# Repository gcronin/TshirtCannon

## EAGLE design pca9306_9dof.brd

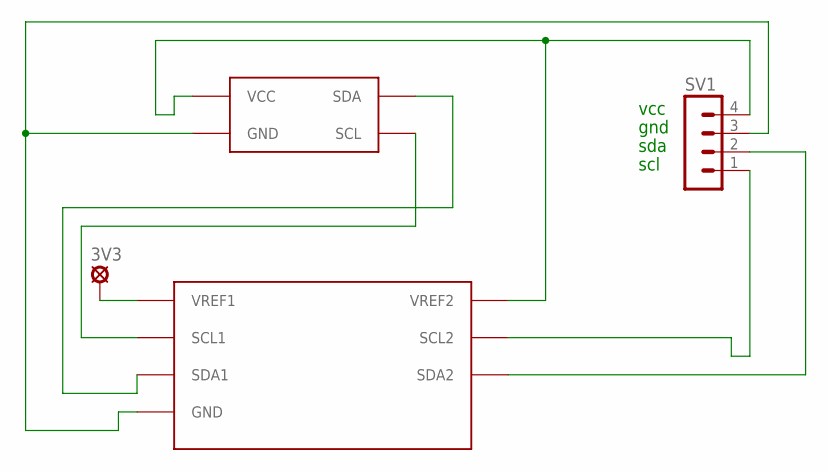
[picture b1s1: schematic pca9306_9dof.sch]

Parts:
3V3: LSP11
SV1: MA04-1
U$1: PCA9306
U$2: 9DOF

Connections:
unnamed: SV1.3, U$1.GND, U$2.GND
unnamed: SV1.4, U$1.VREF2, U$2.VCC
unnamed: SV1.2, U$1.SDA2
unnamed: SV1.1, U$1.SCL2
unnamed: U$1.SDA1, U$2.SDA
unnamed: U$1.SCL1, U$2.SCL
unnamed: 3V3.MP, U$1.VREF1

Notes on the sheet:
vcc
gnd
sda
scl

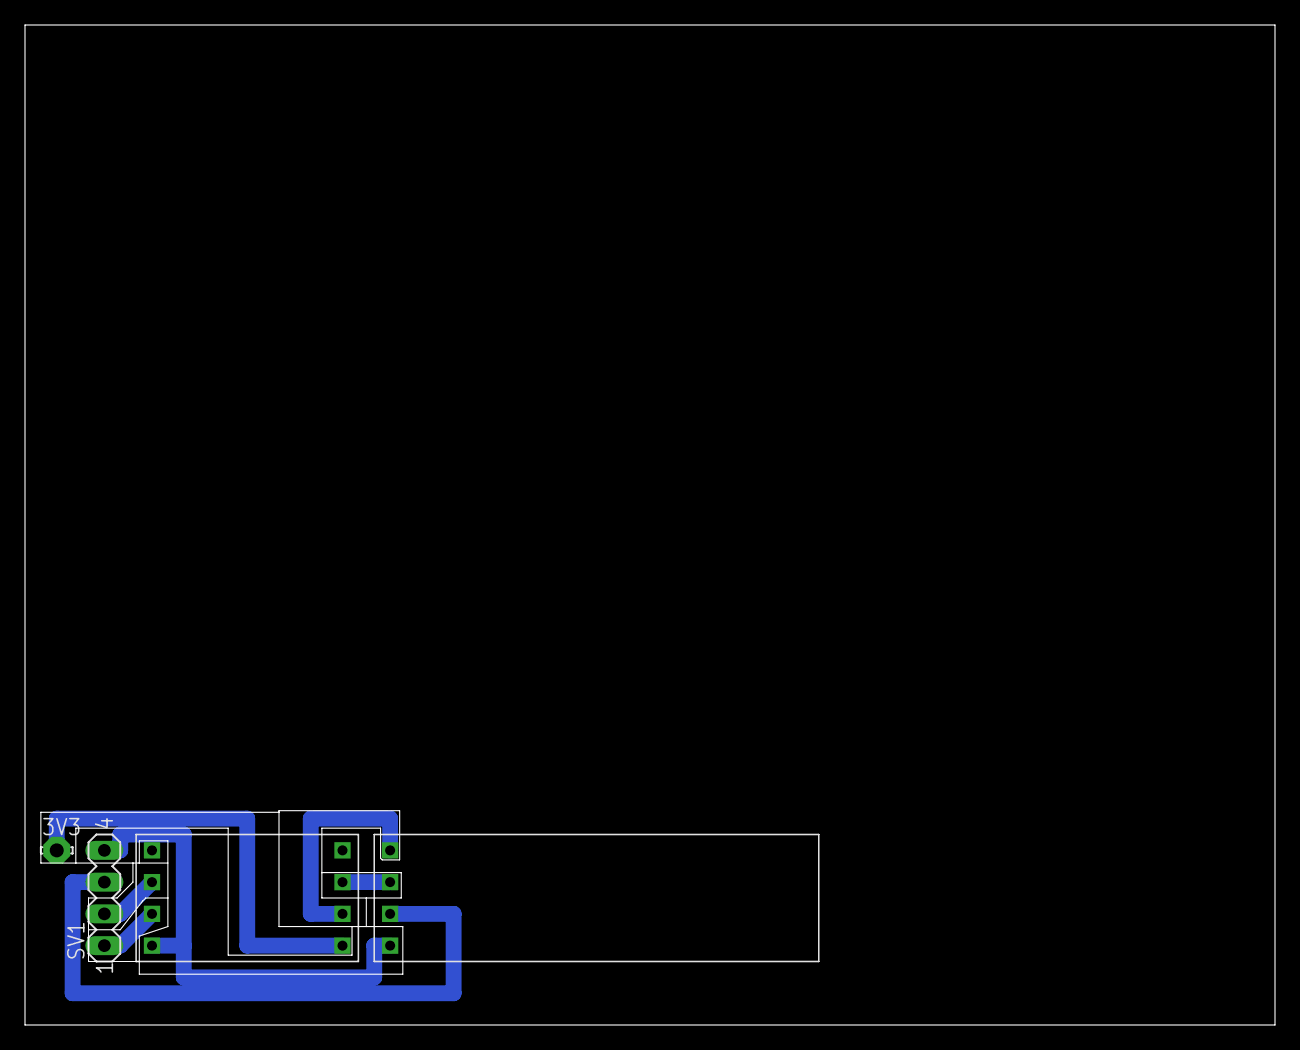
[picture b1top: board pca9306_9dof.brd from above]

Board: 2 copper layers, 100.0 x 80.0 mm, 4 parts (0 on the bottom side), 7 nets.

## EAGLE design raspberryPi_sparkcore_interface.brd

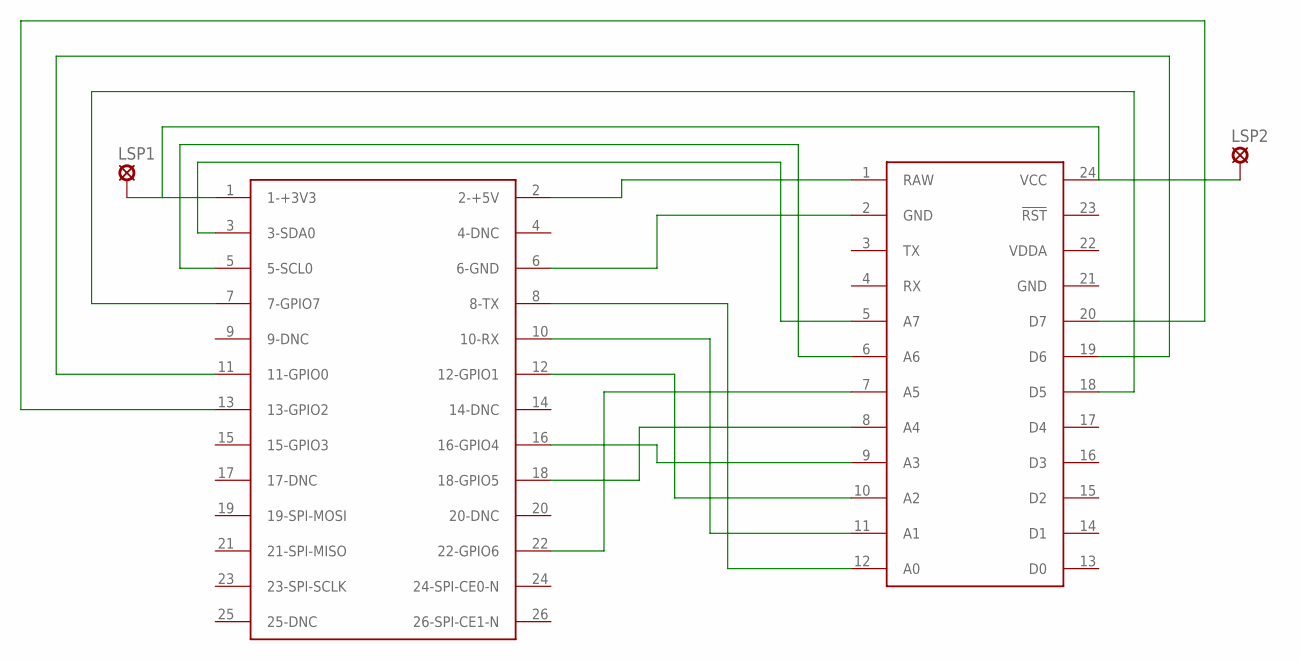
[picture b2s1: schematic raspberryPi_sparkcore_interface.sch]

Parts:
LSP1, LSP2: MCS08
U$1: RASPBERRY-PI
U$2: SPARK_CORECORE; SPARK_CORE

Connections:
GND: U$1.6 (6-GND), U$2.2 (GND), U$2.21 (GND)
unnamed: U$1.2 (2-+5V), U$2.1 (RAW)
unnamed: LSP1.MP, LSP2.MP, U$1.1 (1-+3V3), U$2.24 (VCC)
unnamed: U$1.7 (7-GPIO7), U$2.18 (D5)
unnamed: U$1.11 (11-GPIO0), U$2.19 (D6)
unnamed: U$1.13 (13-GPIO2), U$2.20 (D7)
unnamed: U$1.3 (3-SDA0), U$2.5 (A7)
unnamed: U$1.5 (5-SCL0), U$2.6 (A6)
unnamed: U$1.8 (8-TX), U$2.12 (A0)
unnamed: U$1.10 (10-RX), U$2.11 (A1)
unnamed: U$1.12 (12-GPIO1), U$2.10 (A2)
unnamed: U$1.16 (16-GPIO4), U$2.9 (A3)
unnamed: U$1.18 (18-GPIO5), U$2.8 (A4)
unnamed: U$1.22 (22-GPIO6), U$2.7 (A5)
VDDA: U$2.22 (VDDA)

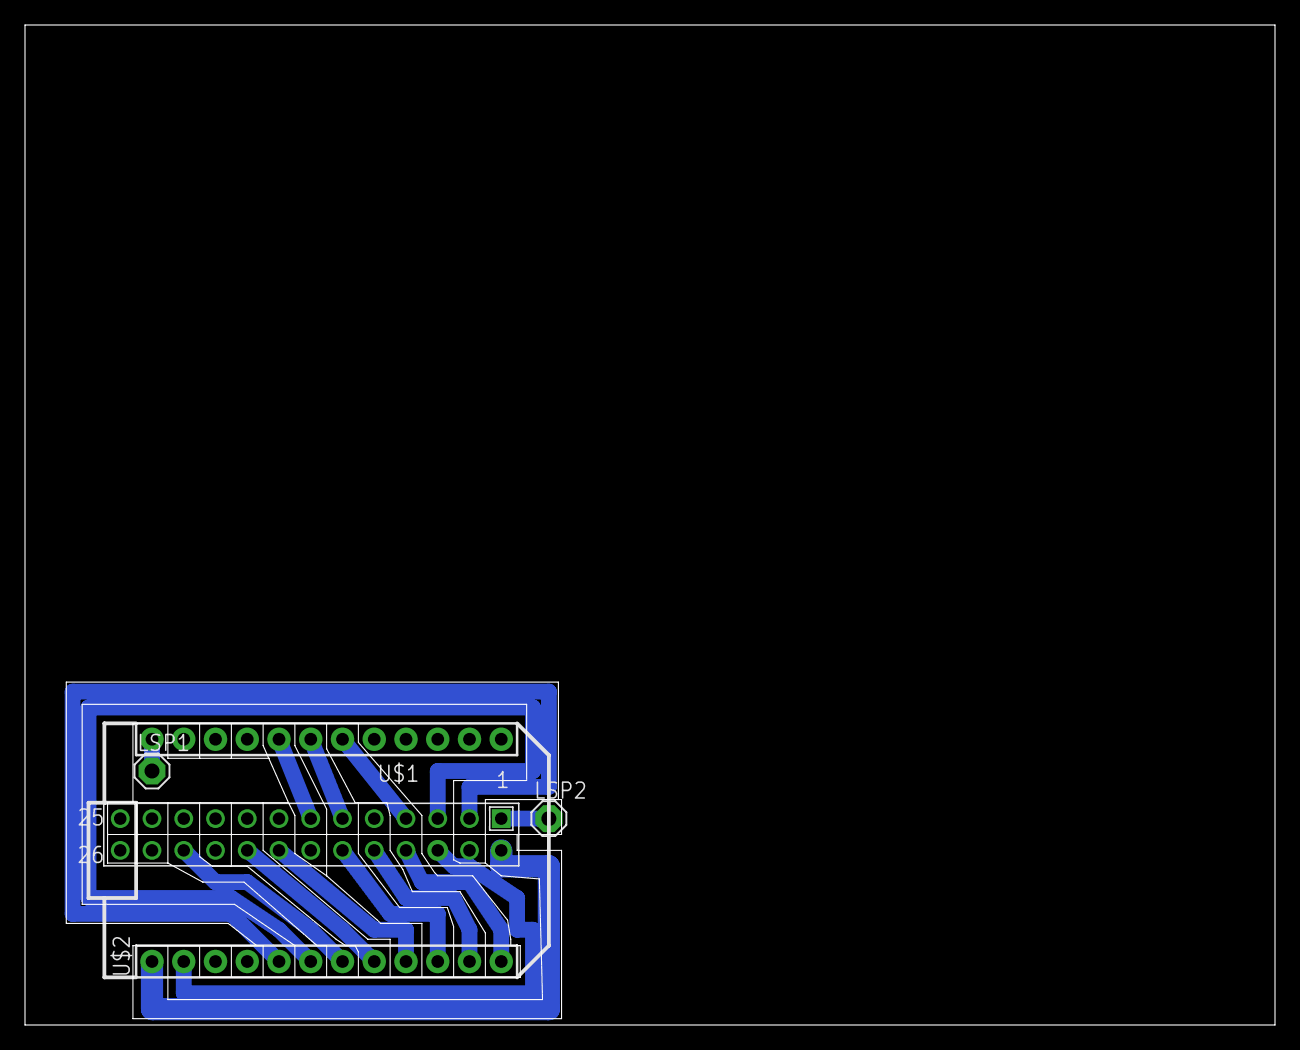
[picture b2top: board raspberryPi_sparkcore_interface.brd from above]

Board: 2 copper layers, 100.0 x 80.0 mm, 4 parts (0 on the bottom side), 14 nets.

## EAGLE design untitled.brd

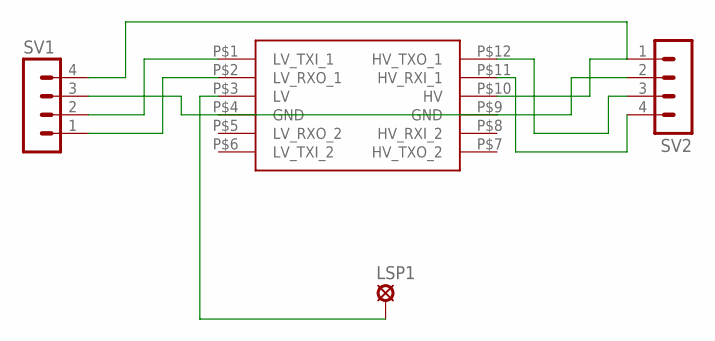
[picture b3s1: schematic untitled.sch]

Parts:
LSP1: MCS08
SV1, SV2: MA04-1
U$1: LOGIC_LEVEL_CONVERTER

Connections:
GND: SV1.3, SV2.2, U$1.P$4 (GND), U$1.P$9 (GND)
unnamed: SV1.1, U$1.P$2 (LV_RXO_1)
unnamed: SV1.2, U$1.P$1 (LV_TXI_1)
unnamed: LSP1.MP, U$1.P$3 (LV)
unnamed: SV1.4, SV2.1, U$1.P$10 (HV)
unnamed: SV2.3, U$1.P$12 (HV_TXO_1)
unnamed: SV2.4, U$1.P$11 (HV_RXI_1)

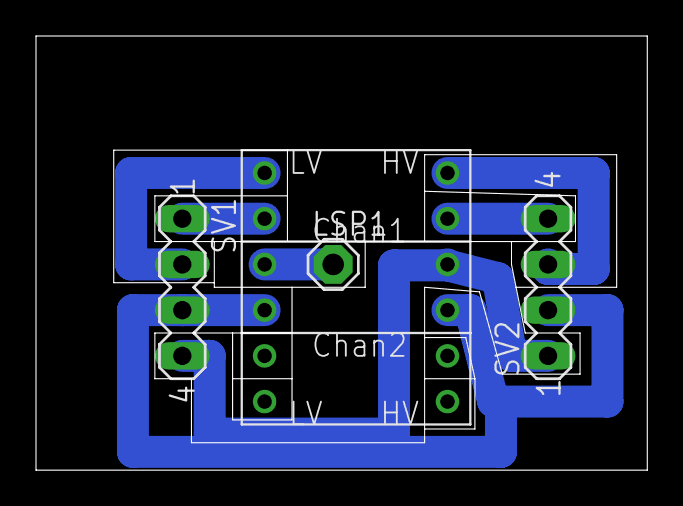
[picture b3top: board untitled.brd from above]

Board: 2 copper layers, 33.9 x 24.1 mm, 4 parts (0 on the bottom side), 7 nets.

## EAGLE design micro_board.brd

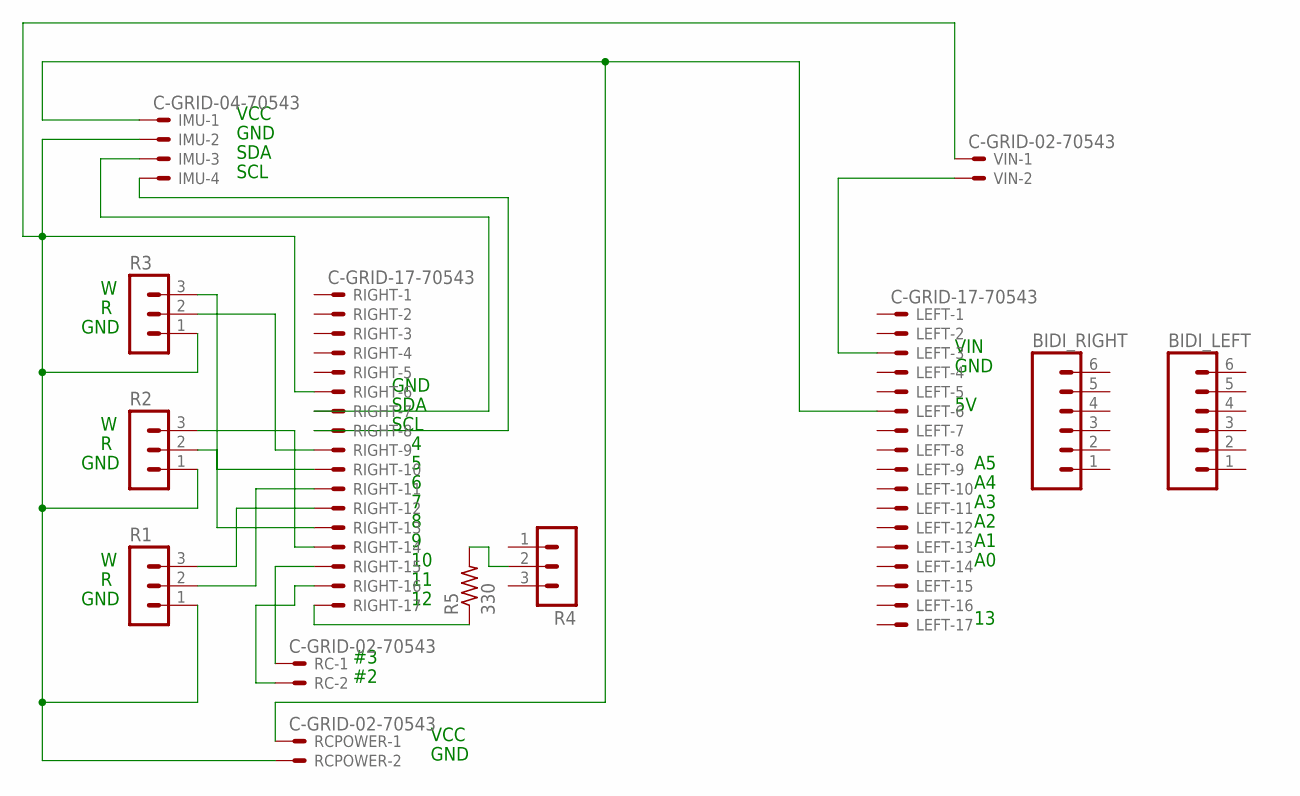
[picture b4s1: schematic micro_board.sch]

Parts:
BIDI_LEFT: M06LONGPADS; 1X06_LONGPADS
BIDI_RIGHT: M06LONGPADS; 1X06_LONGPADS
IMU: C-GRID-04-70543; 70543-04
LEFT: C-GRID-17-70543; 70543-17
R1, R2, R3, R4: MA03-1
R5: 330; 0207/12
RC: C-GRID-02-70543; 70543-02
RCPOWER: C-GRID-02-70543; 70543-02
RIGHT: C-GRID-17-70543; 70543-17
VIN: C-GRID-02-70543; 70543-02

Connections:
5V: IMU.1, LEFT.6, RCPOWER.1
GND: IMU.2, R1.1, R2.1, R3.1, RCPOWER.2, RIGHT.6, VIN.1
unnamed: R3.2, RIGHT.9
unnamed: R2.2, RIGHT.10
unnamed: R1.2, RIGHT.11
unnamed: R1.3, RIGHT.12
unnamed: R3.3, RIGHT.13
unnamed: R2.3, RIGHT.14
unnamed: IMU.3, RIGHT.7
unnamed: IMU.4, RIGHT.8
unnamed: RC.1, RIGHT.15
unnamed: RC.2, RIGHT.16
unnamed: R5.1, RIGHT.17
unnamed: R4.2, R5.2
unnamed: LEFT.3, VIN.2

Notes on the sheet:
GND
SDA
SCL
VIN
VCC

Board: 2 copper layers, 13 parts (0 on the bottom side), 15 nets, no tracks yet.

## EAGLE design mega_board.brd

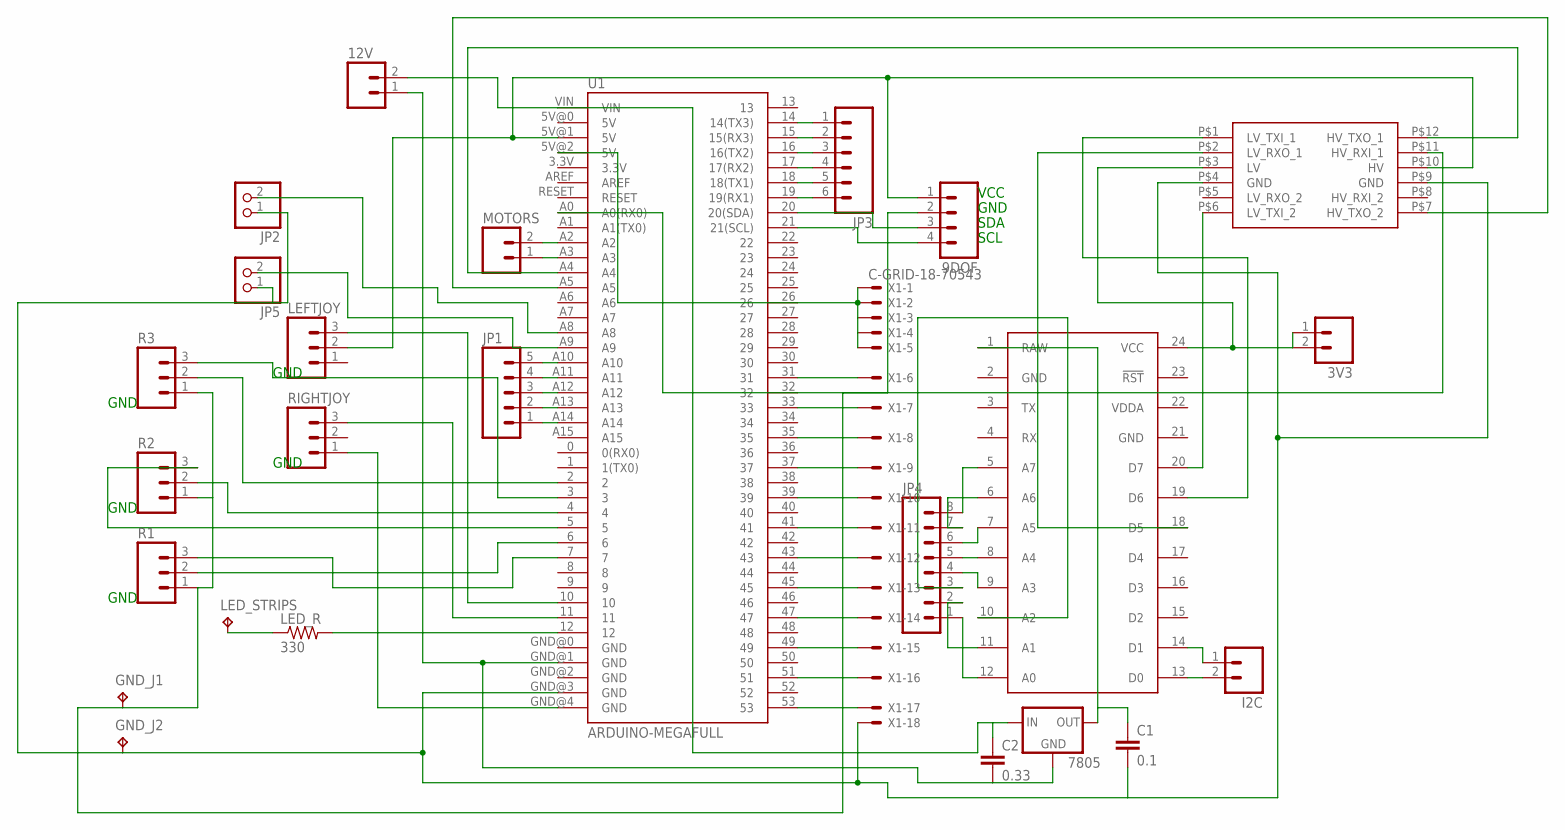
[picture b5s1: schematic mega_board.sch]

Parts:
3V3, 12V: M02PTH3; 1X02_LONGPADS
9DOF: M04LONGPADS; 1X04_LONGPADS
7805: V_REG_78XXSIDE; 78XXL
C1: 0.1; C050-024X044
C2: 0.33; C050-024X044
GND_J1, GND_J2: TPPAD1-17; P1-17
I2C: M02PTH3; 1X02_LONGPADS
JP1: M05PTH_LONGPADS; 1X05_LONGPADS
JP2, JP5: PINHD-1X2; 1X02
JP3: M06LONGPADS; 1X06_LONGPADS
JP4: M08LONGPADS; 1X08_LONGPADS
LED_R: 330; 0207/10
LED_STRIPS: TPPAD1-17; P1-17
LEFTJOY: M03LONGPADS; 1X03_LONGPADS
MOTORS: M02PTH3; 1X02_LONGPADS
R1, R2, R3: M03LONGPADS; 1X03_LONGPADS
RIGHTJOY: M03LONGPADS; 1X03_LONGPADS
U1: ARDUINO-MEGAFULL; ARDUINO_MEGA
U$1: SPARK_CORECORE; SPARK_CORE
U$2: LOGIC_LEVEL_CONVERTER
X1: C-GRID-18-70543; 70543-18

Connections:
5V: 9DOF.1, LEFTJOY.2, U1.5V@1 (5V), U$2.P$10 (HV)
GND: C1.2, GND_J2.TP, JP2.1, JP5.1, U1.GND@3 (GND), U$1.2 (GND), U$1.21 (GND), U$2.P$4 (GND), U$2.P$9 (GND), X1.18
unnamed: 9DOF.4, U1.21 (21(SCL))
unnamed: 9DOF.3, U1.20 (20(SDA))
unnamed: 3V3.1, 3V3.2, U$1.24 (VCC), U$2.P$3 (LV)
unnamed: RIGHTJOY.3, U1.11
unnamed: U1.A4, U$2.P$12 (HV_TXO_1)
unnamed: U1.A5, U$2.P$7 (HV_TXO_2)
unnamed: U$1.20 (D7), U$2.P$6 (LV_TXI_2)
unnamed: U$1.19 (D6), U$2.P$1 (LV_TXI_1)
unnamed: LEFTJOY.3, U1.10
unnamed: JP3.1, U1.14 (14(TX3))
unnamed: JP3.2, U1.15 (15(RX3))
unnamed: JP3.3, U1.16 (16(TX2))
unnamed: JP3.4, U1.17 (17(RX2))
unnamed: JP3.5, U1.18 (18(TX1))
unnamed: JP3.6, U1.19 (19(RX1))
unnamed: JP2.2, U1.A8
unnamed: JP5.2, U1.A9
unnamed: JP1.5, U1.A10
unnamed: JP1.4, U1.A11
unnamed: JP1.3, U1.A12
unnamed: JP1.2, U1.A13
unnamed: JP1.1, U1.A14
unnamed: 12V.2, 7805.IN, C2.1, U1.VIN
unnamed: 12V.1, 7805.GND, C2.2, U1.GND@1 (GND)
unnamed: JP4.8, U$1.5 (A7)
unnamed: JP4.7, U$1.6 (A6)
unnamed: JP4.6, U$1.7 (A5)
unnamed: JP4.5, U$1.8 (A4)
unnamed: JP4.4, U$1.9 (A3)
unnamed: JP4.1, U$1.12 (A0)
unnamed: JP4.2, U$1.11 (A1)
unnamed: JP4.3, U$1.10 (A2)
unnamed: I2C.2, U$1.13 (D0)
unnamed: I2C.1, U$1.14 (D1)
unnamed: 7805.OUT, C1.1, U$1.1 (RAW)
unnamed: RIGHTJOY.1, U1.GND@4 (GND)
unnamed: MOTORS.2, U1.A2
unnamed: MOTORS.1, U1.A3
unnamed: LED_R.2, U1.12
unnamed: LED_R.1, LED_STRIPS.TP
unnamed: R3.3, U1.3
unnamed: 9DOF.2, GND_J1.TP, R1.1, R2.1, R3.1
unnamed: R3.2, U1.2
unnamed: R2.2, U1.4
unnamed: R2.3, U1.5
unnamed: R1.2, U1.6
unnamed: R1.3, U1.7
unnamed: U$1.18 (D5), U$2.P$2 (LV_RXO_1)
unnamed: U1.A0 (A0(RX0)), U$2.P$11 (HV_RXI_1)
unnamed: U1.51, X1.16
unnamed: U1.53, X1.17
unnamed: U1.31, X1.6
unnamed: U1.47, X1.14
unnamed: U1.33, X1.7
unnamed: U1.35, X1.8
unnamed: U1.37, X1.9
unnamed: U1.39, X1.10
unnamed: U1.41, X1.11
unnamed: U1.43, X1.12
unnamed: U1.45, X1.13
unnamed: U1.49, X1.15
unnamed: U1.5V@2 (5V), X1.1, X1.2, X1.3, X1.4, X1.5
VDDA: U$1.22 (VDDA)

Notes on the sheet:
VCC
GND
SDA
SCL

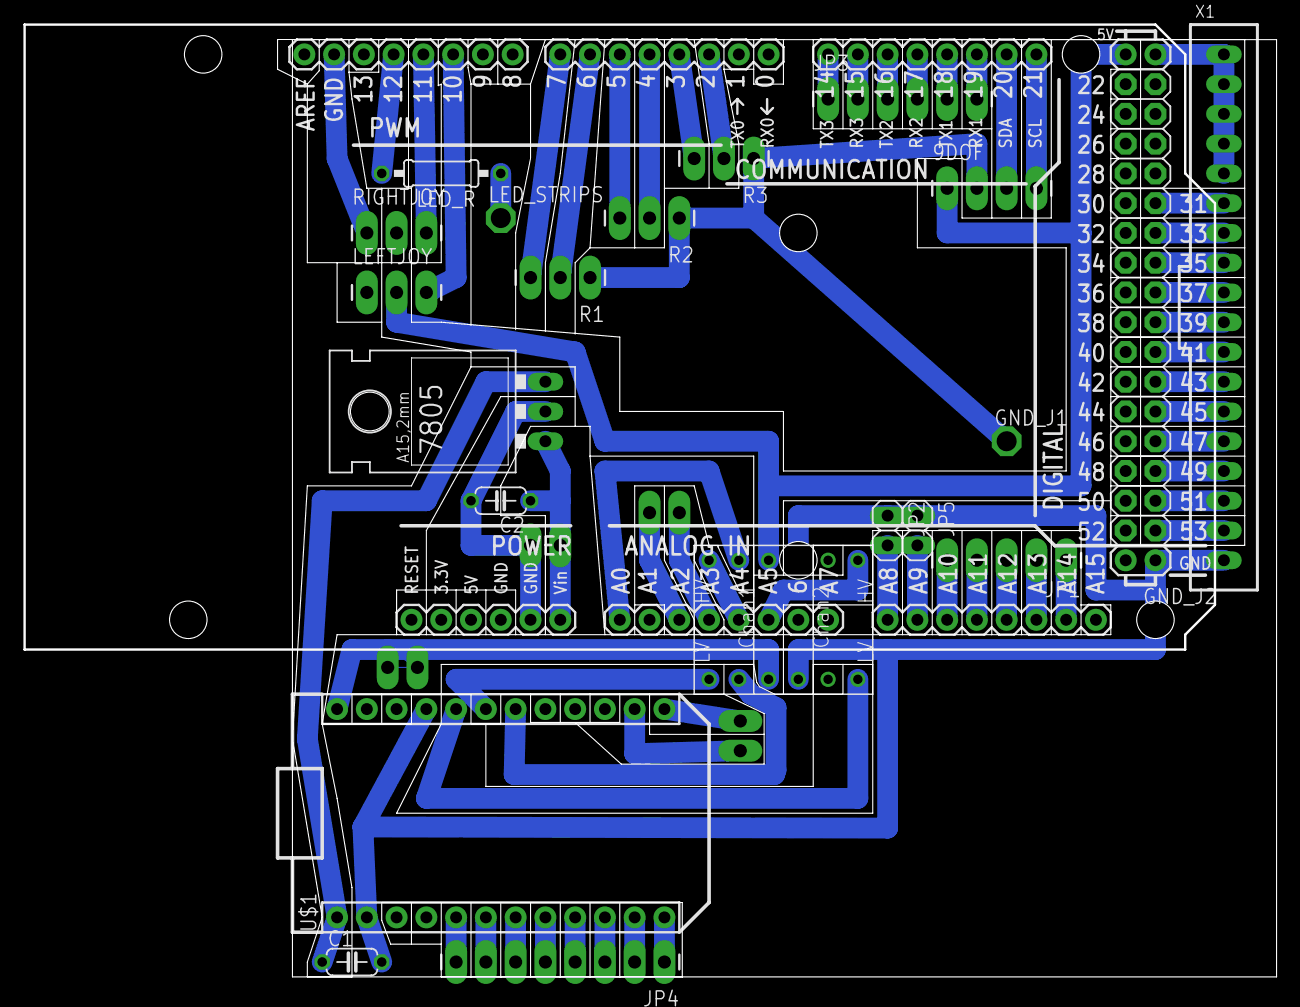
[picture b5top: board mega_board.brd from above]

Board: 2 copper layers, 106.9 x 81.3 mm, 26 parts (0 on the bottom side), 64 nets.

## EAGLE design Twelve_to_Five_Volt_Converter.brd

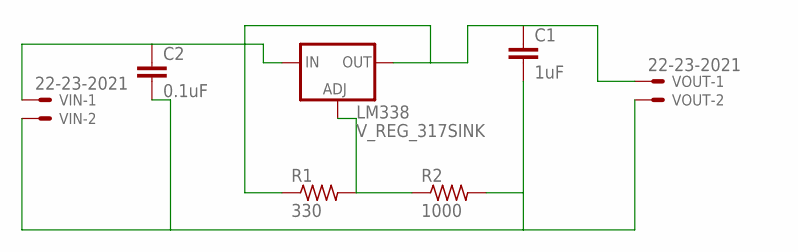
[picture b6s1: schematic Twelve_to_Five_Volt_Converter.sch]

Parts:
C1: 1uF; C5B3.5
C2: 0.1uF; C5B3.5
LM338: V_REG_317SINK; TO220-ADJ
R1: 330; 0207/10
R2: 1000; 0207/10
VIN: 22-23-2021
VOUT: 22-23-2021

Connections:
GND: C1.2, C2.2, R2.2, VIN.2, VOUT.2
unnamed: LM338.ADJ, R1.2, R2.1
unnamed: C1.1, LM338.OUT, R1.1, VOUT.1
unnamed: C2.1, LM338.IN, VIN.1

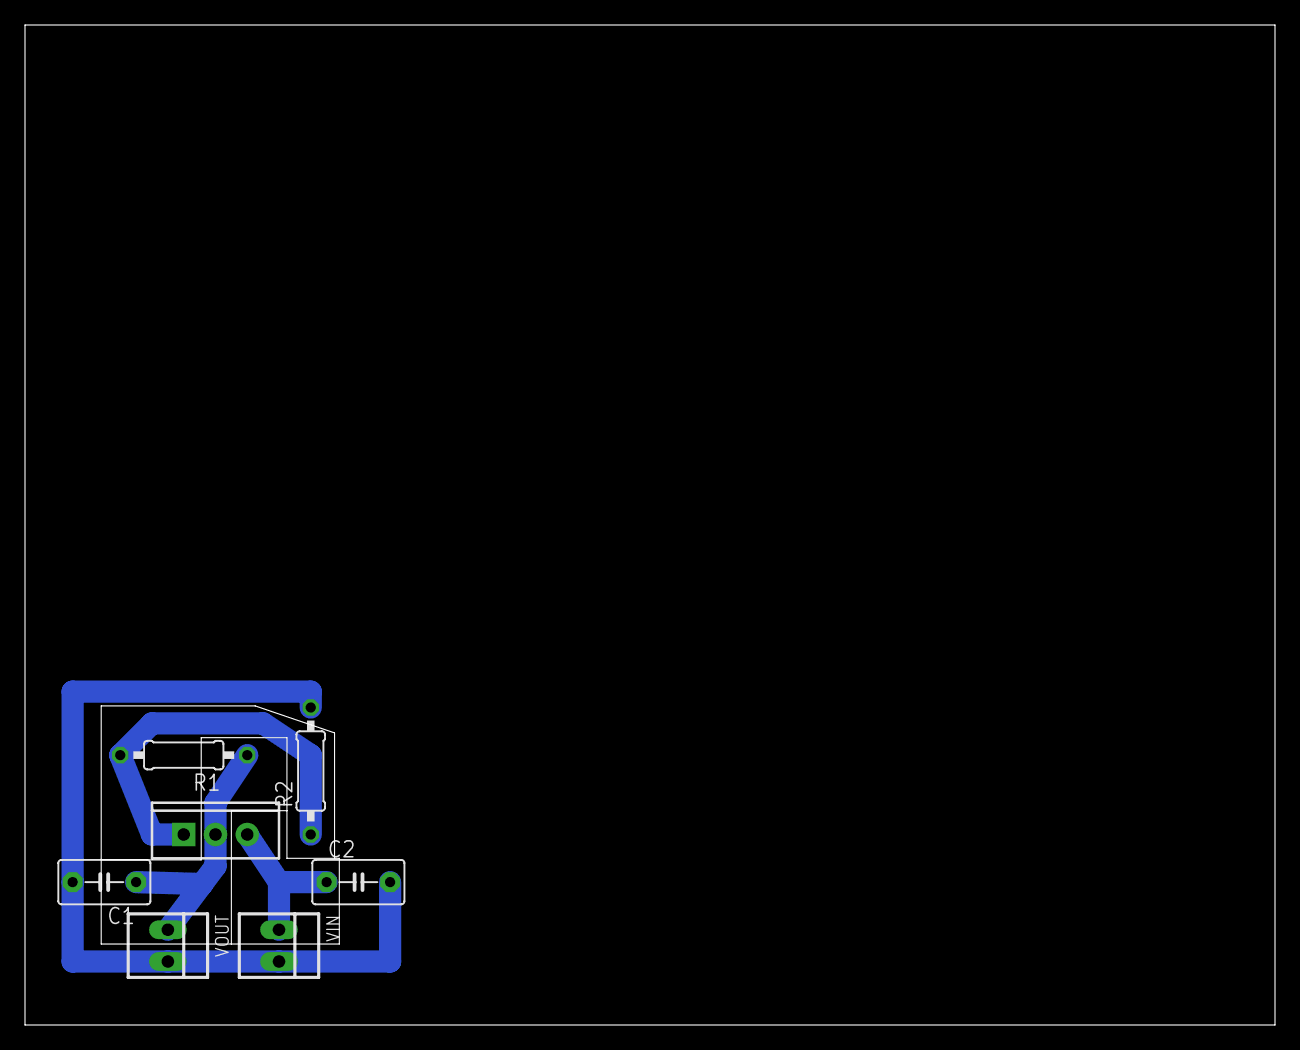
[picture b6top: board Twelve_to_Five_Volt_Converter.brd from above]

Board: 2 copper layers, 100.0 x 80.0 mm, 7 parts (0 on the bottom side), 4 nets.

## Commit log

2014-08-03 Tested Working Pneumatics, IMU, Drive, Cannon
2014-08-03 LED Strip Test Program
2014-08-03 3V to 5V Conversion Tested
2014-08-07 Migrated All File to Mega, Added PCB Files
2014-08-10 Created Drive Program which Read/Serial Writes 9dof
2014-08-31 Added PCB files
2014-09-12 All Pneumatics Test Programs: Untested
2014-09-14 Added pinMode for TshirtValve, Serial Tested Works
2014-09-24 // Once the pressure drops below 60 OR 110 Psi, wait a preset // period of time before we recharge to create some // hysteresis
2014-10-09 Tested Full Drive/Lift/Fire Program RC Controlled

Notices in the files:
parts and their libraries:
SparkFun: Licensing: CC v3.0 Share-Alike You are welcome to use this library for commercial purposes.
SparkFun-Boards: Licensing: Creative Commons ShareAlike 4.0 International - https://creativecommons.org/licenses/by-sa/4.0
